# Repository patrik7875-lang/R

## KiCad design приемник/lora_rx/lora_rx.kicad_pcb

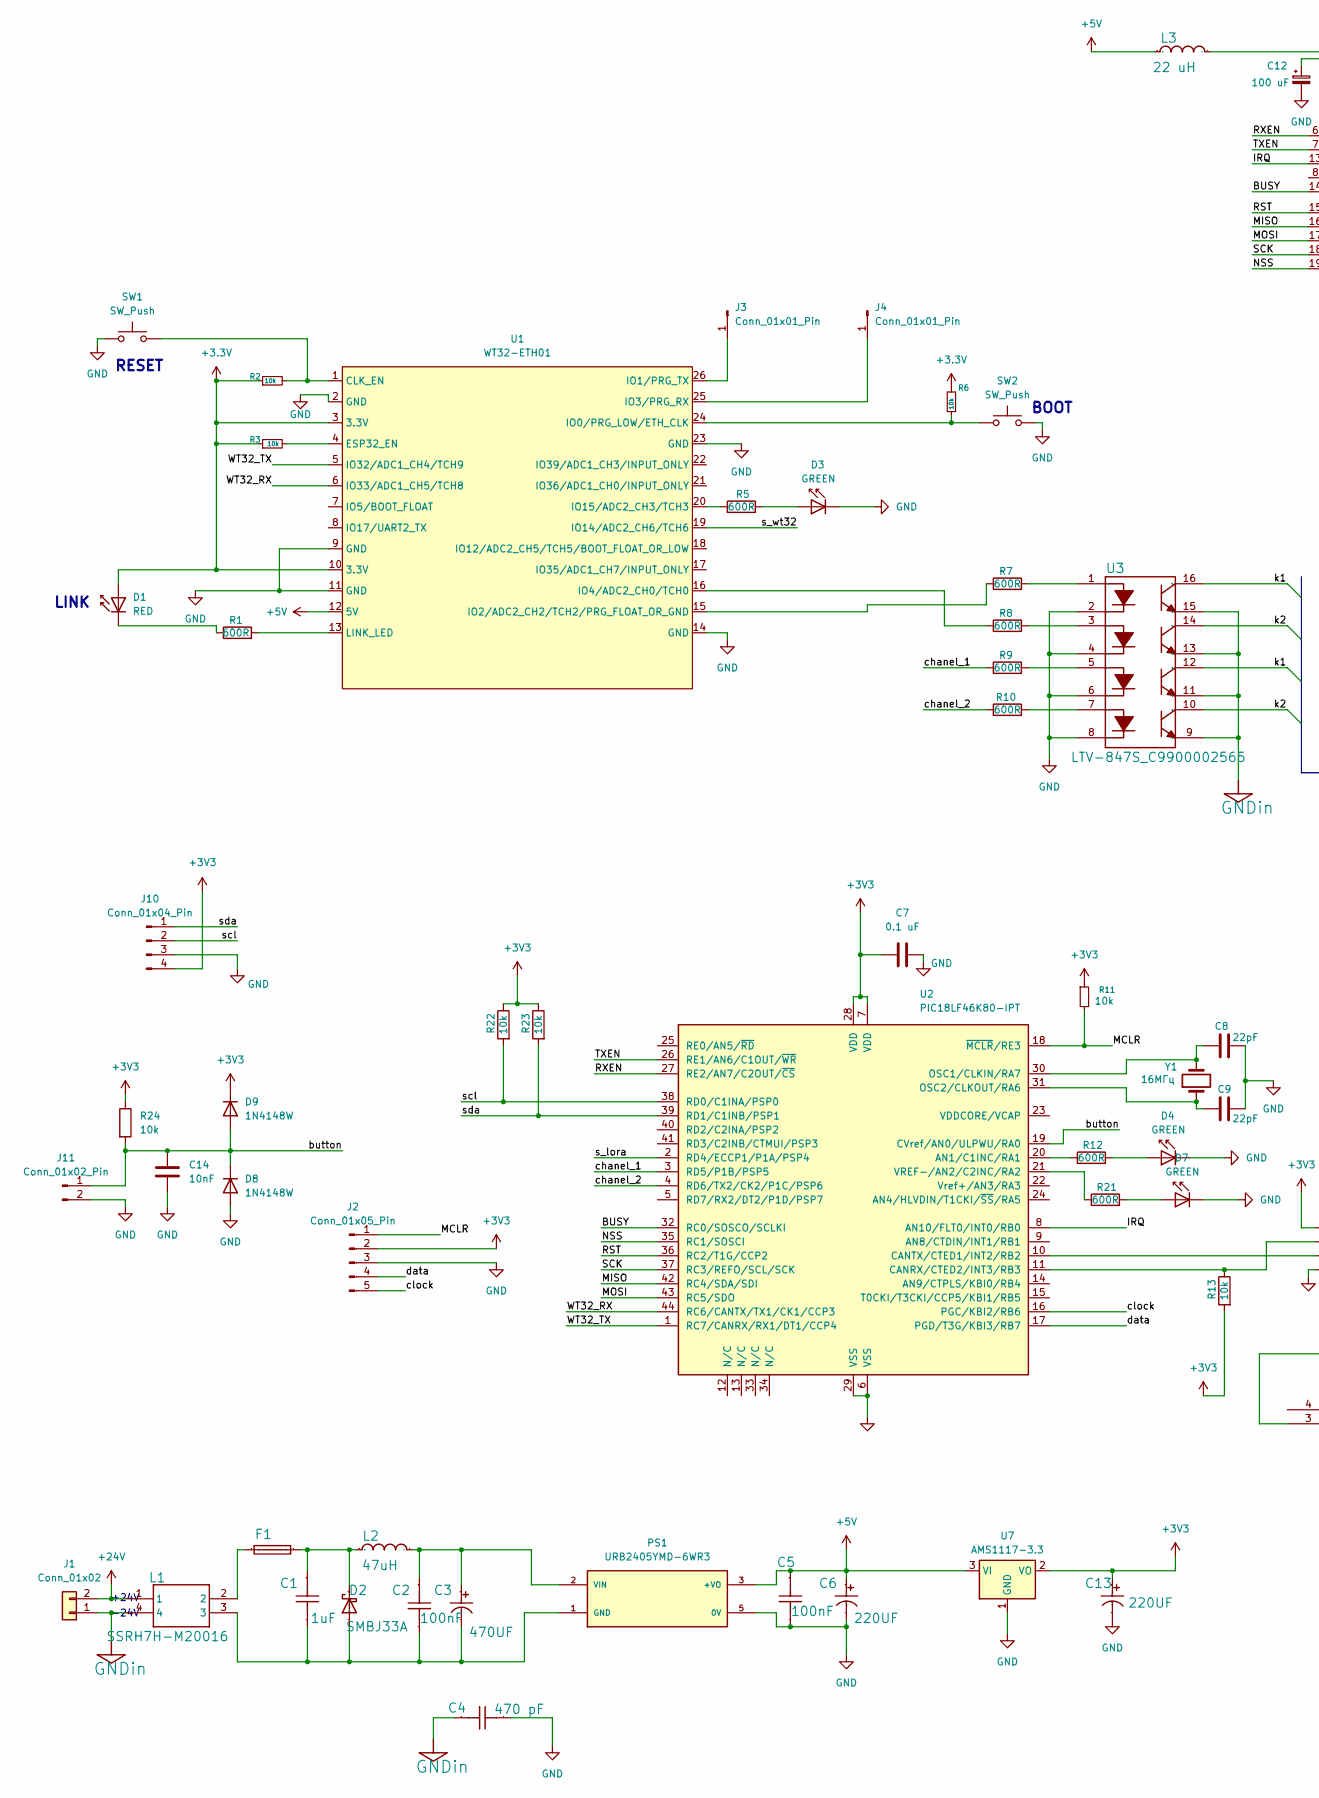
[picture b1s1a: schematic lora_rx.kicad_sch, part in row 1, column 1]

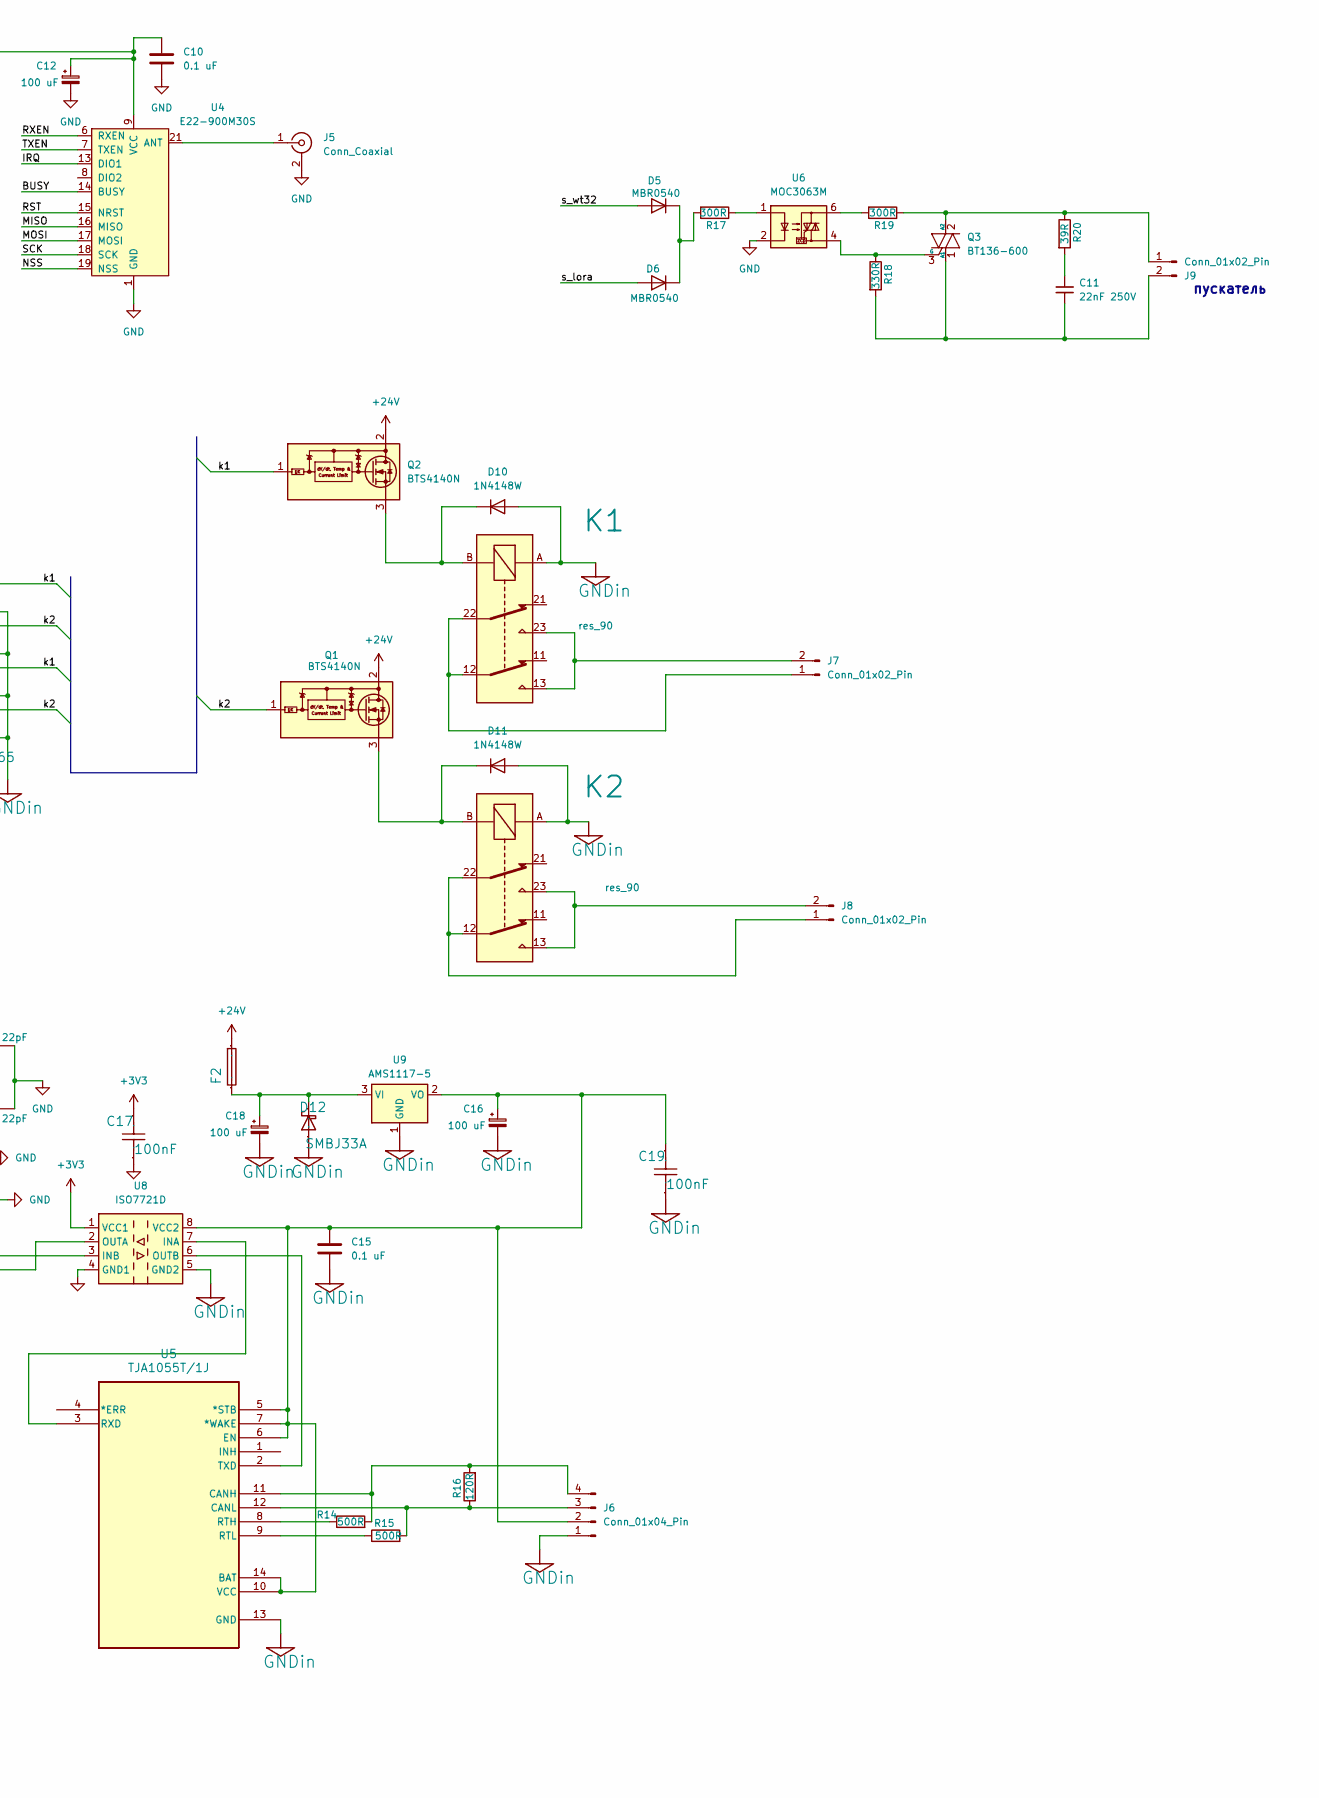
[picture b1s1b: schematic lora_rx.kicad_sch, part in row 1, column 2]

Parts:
C1: 1uF; C_1206_3216Metric; Manufacturer Part FCC0805B104M500DT
C2, C17, C19: 100nF; C_1206_3216Metric; Manufacturer Part FCC0805B104M500DT
C3: 470UF; CP_Radial_D10.0mm_P5.00mm; Manufacturer Part 1000uF/50V
C4: 470 pF; C_Disc_D7.5mm_W5.0mm_P7.50mm; Manufacturer Part FCC0805B104M500DT
C5: 100nF; C_1206_3216Metric; Manufacturer Part Ceramic capacitors47PF 3KV
C6, C13: 220UF; CP_Radial_D10.0mm_P5.00mm; Manufacturer Part 1000uF/50V
C7, C10, C15: 0.1 uF; C_1206_3216Metric
C8, C9: 22pF; C_1206_3216Metric
C11: 22nF 250V; C_Rect_L18.0mm_W5.0mm_P15.00mm_FKS3_FKP3
C12, C16, C18: 100 uF; CP_EIA-7343-31_Kemet-D
C14: 10nF; C_0805_2012Metric
D1: RED; LED_1206_3216Metric
D2, D12: SMBJ33A; D_SMB
D3, D4, D7: GREEN; LED_1206_3216Metric
D5, D6: MBR0540; D_SOD-123
D8, D9, D10, D11: 1N4148W; D_SOD-123
F1: JFC2410-0200FS; fuse holder 2410; Manufacturer Part JFC2410-0200FS
F2: JFC2410-0200FS; Fuse_1206_3216Metric; Manufacturer Part JFC2410-0200FS
J1: Conn_01x02; TerminalBlock_Phoenix_MKDS-1,5-2_1x02_P5.00mm_Horizontal
J2: Conn_01x05_Pin; PinHeader_1x05_P2.54mm_Vertical
J3, J4: Conn_01x01_Pin; PinHeader_1x01_P2.54mm_Vertical
J5: Conn_Coaxial; SMA_Molex_73251-2200_Horizontal
J6: Conn_01x04_Pin; KF141R - 4P
J7, J8: Conn_01x02_Pin; TerminalBlock_Phoenix_MKDS-1,5-2_1x02_P5.00mm_Horizontal
J9: Conn_01x02_Pin; TerminalBlock_MetzConnect_Type701_RT11L02HGLU_1x02_P6.35mm_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
J10: Conn_01x04_Pin; Molex_KK-254_AE-6410-04A_1x04_P2.54mm_Vertical
J11: Conn_01x02_Pin; JST_PH_B2B-PH-K_1x02_P2.00mm_Vertical
K1, K2: res_90; res90
L1: SSRH7H-M20016
L2: 47uH; L_12x12mm_H6mm; Manufacturer Part CYL104R-10UH
L3: 22 uH; L_TracoPower_TCK-047_5.2x5.8mm; Manufacturer Part CYL104R-10UH
PS1: URB2405YMD-6WR3; CONV_URB2405YMD-6WR3; PARTREV 2020.11.20-A/9
Q1, Q2: BTS4140N; SOT-223
Q3: BT136-600; TO-220-3_Vertical
R1, R5, R7, R8, R9, R10, R12, R21: 600R; LED_0805_2012Metric
R2, R3, R6, R11, R13, R22, R23: 10k; R_0805_2012Metric
R14, R15: 500R; R_0805_2012Metric
R16: 120R; R_0805_2012Metric
R17: 300R; R_0805_2012Metric
R18: 330R; R_1206_3216Metric
R19: 300R; R_1206_3216Metric
R20: 39R; R_Axial_DIN0411_L9.9mm_D3.6mm_P5.08mm_Vertical
R24: 10k; C_0805_2012Metric
SW1, SW2: SW_Push; SW_Push_1P1T_NO_Vertical_Wuerth_434133025816
U1: WT32-ETH01; WT32-ETH01_0
U2: PIC18LF46K80-IPT; TQFP-44_10x10mm_P0.8mm
U3: LTV-847S_C9900002565; SMDIP-16_W9.53mm; Manufacturer Part LTV-847S
U4: E22-900M30S; e22-900m30s-handsoldering; LCSC# C411294
U5: TJA1055T/1J; SO14_SOT108-1_NXP
U6: MOC3063M; SMDIP-6_W9.53mm
U7: AMS1117-3.3; SOT-223-3_TabPin2
U8: ISO7721D; SOIC-8_3.9x4.9mm_P1.27mm
U9: AMS1117-5; SOT-223-3_TabPin2
Y1: 16МГц; Crystal_HC18-U_Vertical

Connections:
+3.3V: D1.2 (A), R2.1, R3.1, R6.2, U1.3 (3.3V), U1.10 (3.3V)
+3V3: C7.1, C13.1, C17.1, D9.1 (K), J2.2, J10.4, R11.1, R13.2, R22.1, R23.1, R24.1, U2.7 (VDD), U2.28 (VDD), U7.2 (VO), U8.1 (VCC1)
+5V: C5.1, C6.1, L3.1, PS1.3 (+VO), U1.12 (5V), U7.3 (VI)
+24V: F2.1, J1.2, L1.1, Q1.2 (V_{bb}), Q1.4 (V_{bb}), Q2.2 (V_{bb}), Q2.4 (V_{bb})
/BUSY: U2.32 (RC0/SOSCO/SCLKI), U4.14 (BUSY)
/IRQ: U2.8 (AN10/FLT0/INT0/RB0), U4.13 (DIO1)
/MCLR: J2.1, R11.2, U2.18 (~MCLR/RE3)
/MISO: U2.42 (RC4/SDA/SDI), U4.16 (MISO)
/MOSI: U2.43 (RC5/SDO), U4.17 (MOSI)
/NSS: U2.35 (RC1/SOSCI), U4.19 (NSS)
/RST: U2.36 (RC2/T1G/CCP2), U4.15 (NRST)
/RXEN: U2.27 (RE2/AN7/C2OUT/~CS), U4.6 (RXEN)
/SCK: U2.37 (RC3/REFO/SCL/SCK), U4.18 (SCK)
/TXEN: U2.26 (RE1/AN6/C1OUT/~WR), U4.7 (TXEN)
/WT32_RX: U1.6 (IO33/ADC1_CH5/TCH8), U2.44 (RC6/CANTX/TX1/CK1/CCP3)
/WT32_TX: U1.5 (IO32/ADC1_CH4/TCH9), U2.1 (RC7/CANRX/RX1/DT1/CCP4)
/button: C14.1, D8.1 (K), D9.2 (A), J11.1, R24.2, U2.19 (CVref/AN0/ULPWU/RA0)
/chanel_1: R9.1, U2.3 (RD5/P1B/PSP5)
/chanel_2: R10.1, U2.4 (RD6/TX2/CK2/P1C/PSP6)
/clock: J2.5, U2.16 (PGC/KBI2/RB6)
/data: J2.4, U2.17 (PGD/T3G/KBI3/RB7)
/k1: Q2.1 (IN), U3.12 (COL3), U3.16 (COL1)
/k2: Q1.1 (IN), U3.10 (COL4), U3.14 (COL2)
/s_lora: D6.2 (A), U2.2 (RD4/ECCP1/P1A/PSP4)
/s_wt32: D5.2 (A), U1.19 (IO14/ADC2_CH6/TCH6)
/scl: J10.2, R22.2, U2.38 (RD0/C1INA/PSP0)
/sda: J10.1, R23.2, U2.39 (RD1/C1INB/PSP1)
GND: C4.2, C5.2, C6.2, C7.2, C8.2, C9.1, C10.1, C12.2, C13.2, C14.2, C17.2, D3.1 (K), D4.1 (K), D7.1 (K), D8.2 (A), J2.3, J5.2 (Ext), J10.3, J11.2, PS1.5 (0V), SW1.2, SW2.2, U1.2 (GND), U1.9 (GND), U1.11 (GND), U1.14 (GND), U1.23 (GND), U2.6 (VSS), U2.29 (VSS), U3.2 (CAT1), U3.4 (CAT2), U3.6 (CAT3), U3.8 (CAT4), U4.1 (GND), U4.2 (GND), U4.3 (GND), U4.4 (GND), U4.5 (GND), U4.11 (GND), U4.12 (GND), U4.20 (GND), U4.22 (GND), U6.2, U7.1 (GND), U8.4 (GND1)
GNDin: C4.1, C15.1, C16.2, C18.2, C19.2, D10.2 (A), D11.2 (A), D12.2 (A), J1.1, J6.1, K1.A, K2.A, L1.4, U3.9 (EM4), U3.11 (EM3), U3.13 (EM2), U3.15 (EM1), U5.13 (GND), U8.5 (GND2), U9.1 (GND)
unnamed: C11.1, R20.2
unnamed: D1.1 (K), R1.1
unnamed: C1.2, C2.2, C3.2, D2.2 (A), L1.3, PS1.1 (GND)
unnamed: C1.1, D2.1 (K), F1.1, L2.1
unnamed: D3.2 (A), R5.1
unnamed: D4.2 (A), R12.1
unnamed: D5.1 (K), D6.1 (K), R17.2
unnamed: D7.2 (A), R21.1
unnamed: D10.1 (K), K1.B, Q2.3 (OUT)
unnamed: D11.1 (K), K2.B, Q1.3 (OUT)
unnamed: C18.1, D12.1 (K), F2.2, U9.3 (VI)
unnamed: F1.2, L1.2
unnamed: J3.1 (Pin_1_1), U1.26 (IO1/PRG_TX)
unnamed: J4.1 (Pin_1_1), U1.25 (IO3/PRG_RX)
unnamed: J5.1 (In), U4.21 (ANT)
unnamed: C15.2, C16.1, C19.1, J6.2, U5.5 (*STB), U5.6 (EN), U5.7 (*WAKE), U5.10 (VCC), U5.14 (BAT), U8.8 (VCC2), U9.2 (VO)
unnamed: J6.3, R15.2, R16.1, U5.12 (CANL)
unnamed: J6.4, R14.2, R16.2, U5.11 (CANH)
unnamed: J7.1, K1.12, K1.22
unnamed: J7.2, K1.13, K1.23
unnamed: J8.1, K2.12, K2.22
unnamed: J8.2, K2.13, K2.23
unnamed: J9.1, Q3.2 (A2), R19.1, R20.1
unnamed: C11.2, J9.2, Q3.1 (A1), R18.2
unnamed: C2.1, C3.1, L2.2, PS1.2 (VIN)
unnamed: Q3.3 (G), R18.1, U6.4
unnamed: R17.1, U6.1
unnamed: R19.2, U6.6
unnamed: R2.2, SW1.1, U1.1 (CLK_EN)
unnamed: R3.2, U1.4 (ESP32_EN)
unnamed: R6.1, SW2.1, U1.24 (IO0/PRG_LOW/ETH_CLK)
unnamed: R7.1, U1.15 (IO2/ADC2_CH2/TCH2/PRG_FLOAT_OR_GND)
unnamed: R8.1, U1.16 (IO4/ADC2_CH0/TCH0)
unnamed: R5.2, U1.20 (IO15/ADC2_CH3/TCH3)
unnamed: R1.2, U1.13 (LINK_LED)
unnamed: R12.2, U2.20 (AN1/C1INC/RA1)
unnamed: R13.1, U2.11 (CANRX/CTED2/INT3/RB3), U8.2 (OUTA)
unnamed: U2.10 (CANTX/CTED1/INT2/RB2), U8.3 (INB)
unnamed: C8.1, U2.30 (OSC1/CLKIN/RA7), Y1.2
unnamed: C9.2, U2.31 (OSC2/CLKOUT/RA6), Y1.1
unnamed: R21.2, U2.21 (VREF-/AN2/C2INC/RA2)
unnamed: R7.2, U3.1 (AN1)
unnamed: R8.2, U3.3 (AN2)
unnamed: R9.2, U3.5 (AN3)
unnamed: R10.2, U3.7 (AN4)
unnamed: R14.1, U5.8 (RTH)
unnamed: R15.1, U5.9 (RTL)
unnamed: U5.3 (RXD), U8.7 (INA)
unnamed: U5.2 (TXD), U8.6 (OUTB)
VCC: C10.2, C12.1, L3.2, U4.9 (VCC), U4.10 (VCC)

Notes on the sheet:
+24V
-24V
пускатель
LINK
RESET
BOOT

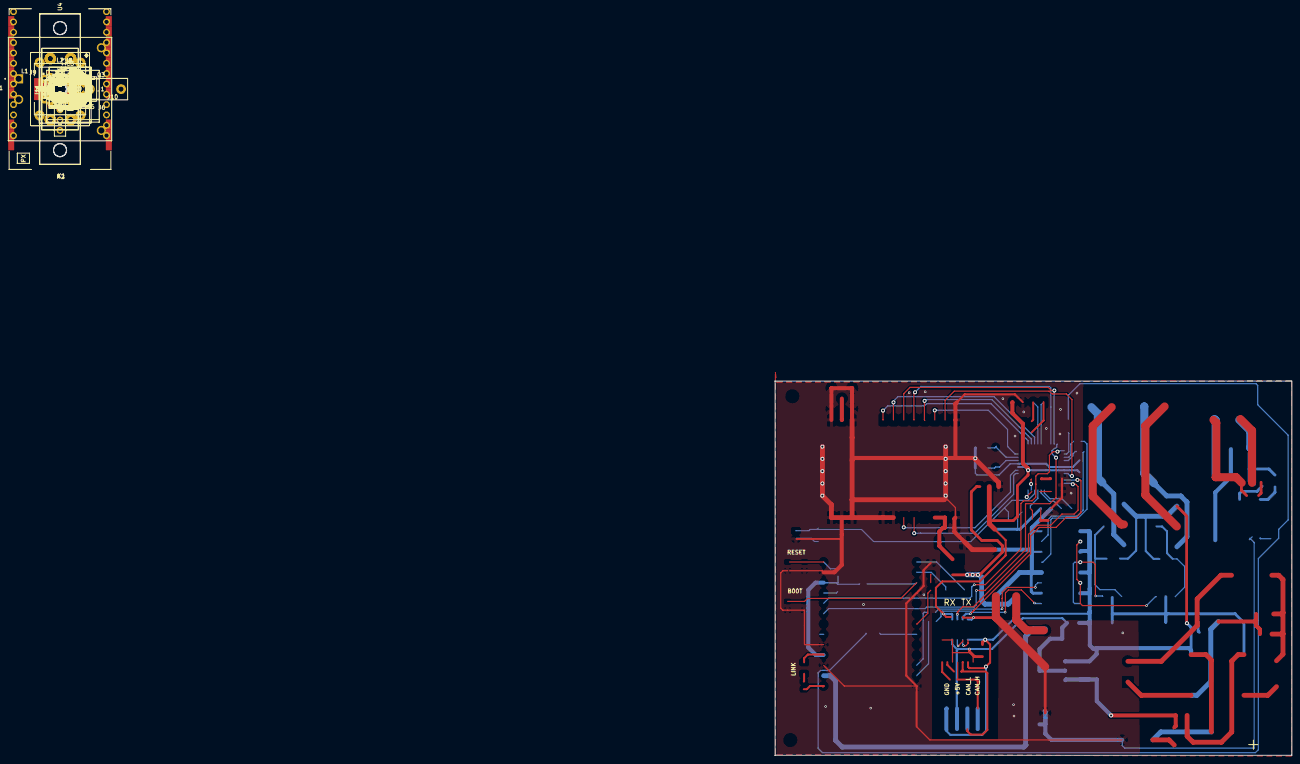
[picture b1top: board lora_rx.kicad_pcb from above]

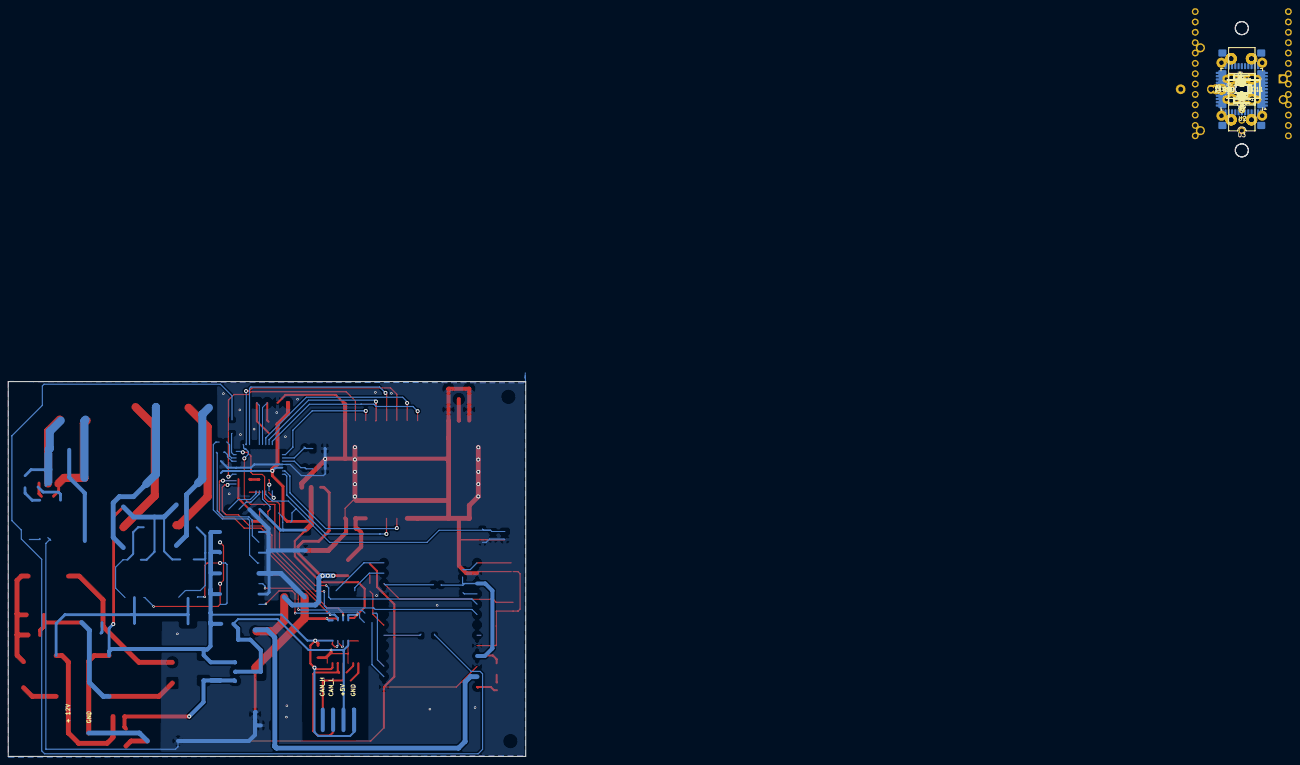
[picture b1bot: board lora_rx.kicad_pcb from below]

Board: 2 copper layers, 88 parts (33 on the bottom side), 79 nets.
